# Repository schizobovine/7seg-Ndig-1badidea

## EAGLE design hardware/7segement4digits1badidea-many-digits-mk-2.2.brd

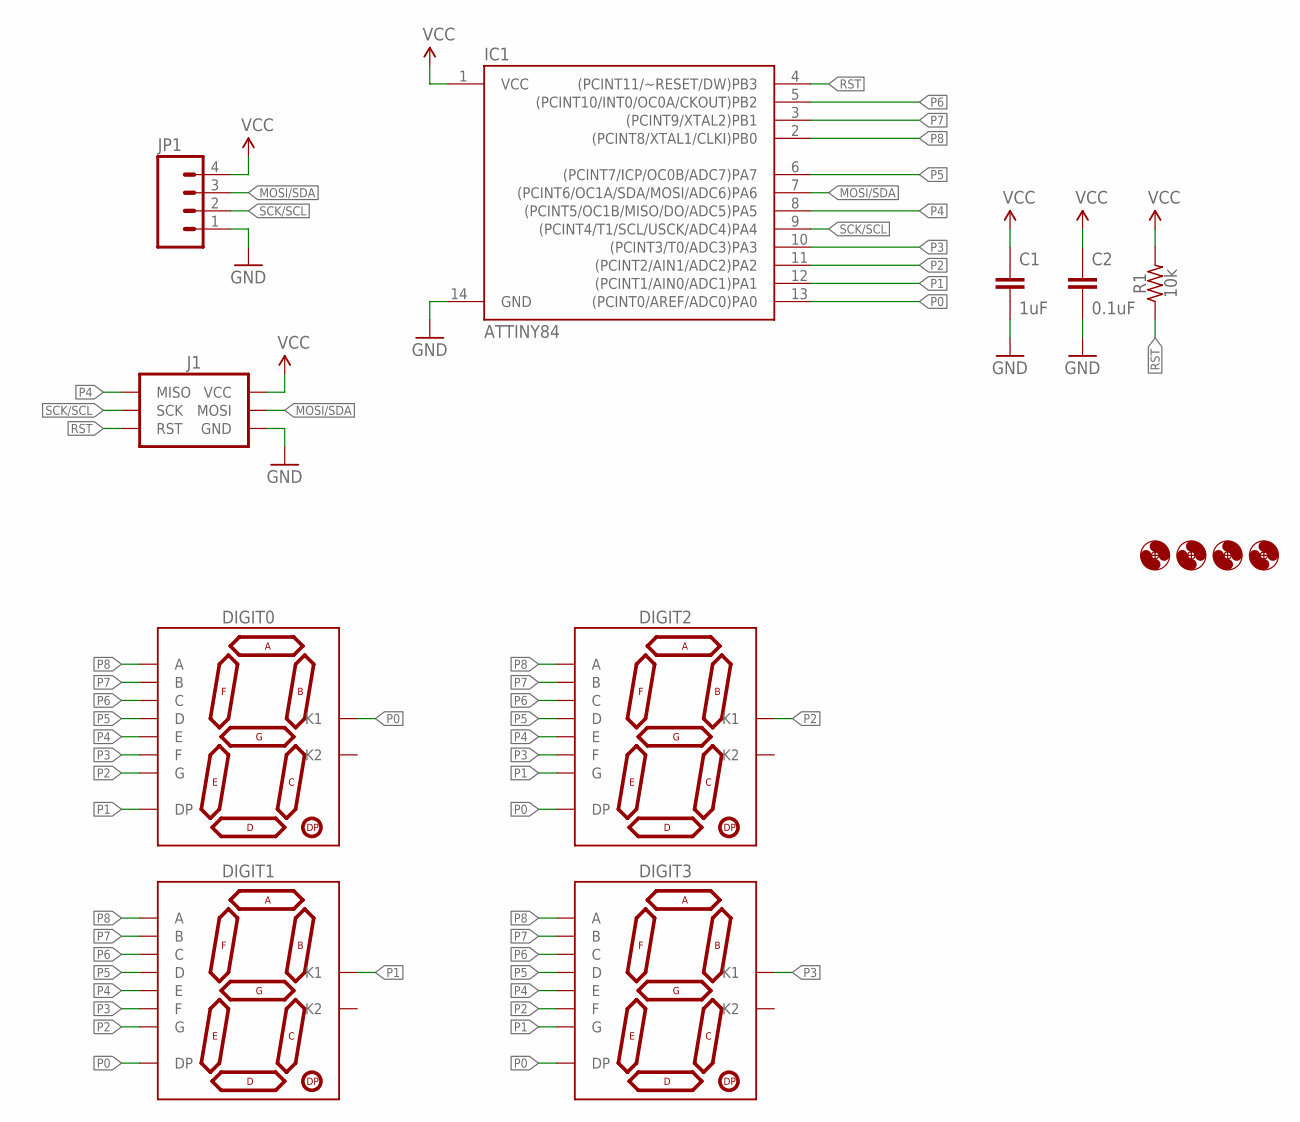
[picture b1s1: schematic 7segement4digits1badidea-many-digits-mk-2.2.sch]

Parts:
C1: 1uF; C0805
C2: 0.1uF; C0603
DIGIT0, DIGIT1, DIGIT2, DIGIT3: 7SEG_1DIGPTH-25.4MM; 7SEG_1DIG_25.4MM
H1, H2, H3, H4: HOLE#2; HOLE-#2
IC1: ATTINY84; SO14
J1: AVR_SPI_PRG_6PTH; 2X3
JP1: M04PTH; 1X04-PTH-VERT
R1: 10k; R0603

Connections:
GND: C1.2, C2.2, IC1.14 (GND), J1.6 (GND), JP1.1
MOSI/SDA: IC1.7 ((PCINT6/OC1A/SDA/MOSI/ADC6)PA6), J1.4 (MOSI), JP1.3
P0: DIGIT0.3 (K1), DIGIT1.5 (DP), DIGIT2.5 (DP), DIGIT3.5 (DP), IC1.13 ((PCINT0/AREF/ADC0)PA0)
P1: DIGIT0.5 (DP), DIGIT1.3 (K1), DIGIT2.10 (G), DIGIT3.10 (G), IC1.12 ((PCINT1/AIN0/ADC1)PA1)
P2: DIGIT0.10 (G), DIGIT1.10 (G), DIGIT2.3 (K1), DIGIT3.9 (F), IC1.11 ((PCINT2/AIN1/ADC2)PA2)
P3: DIGIT0.9 (F), DIGIT1.9 (F), DIGIT2.9 (F), DIGIT3.3 (K1), IC1.10 ((PCINT3/T0/ADC3)PA3)
P4: DIGIT0.1 (E), DIGIT1.1 (E), DIGIT2.1 (E), DIGIT3.1 (E), IC1.8 ((PCINT5/OC1B/MISO/DO/ADC5)PA5), J1.1 (MISO)
P5: DIGIT0.2 (D), DIGIT1.2 (D), DIGIT2.2 (D), DIGIT3.2 (D), IC1.6 ((PCINT7/ICP/OC0B/ADC7)PA7)
P6: DIGIT0.4 (C), DIGIT1.4 (C), DIGIT2.4 (C), DIGIT3.4 (C), IC1.5 ((PCINT10/INT0/OC0A/CKOUT)PB2)
P7: DIGIT0.6 (B), DIGIT1.6 (B), DIGIT2.6 (B), DIGIT3.6 (B), IC1.3 ((PCINT9/XTAL2)PB1)
P8: DIGIT0.7 (A), DIGIT1.7 (A), DIGIT2.7 (A), DIGIT3.7 (A), IC1.2 ((PCINT8/XTAL1/CLKI)PB0)
RST: IC1.4 ((PCINT11/~RESET/DW)PB3), J1.5 (RST), R1.1
SCK/SCL: IC1.9 ((PCINT4/T1/SCL/USCK/ADC4)PA4), J1.3 (SCK), JP1.2
VCC: C1.1, C2.1, IC1.1 (VCC), J1.2 (VCC), JP1.4, R1.2

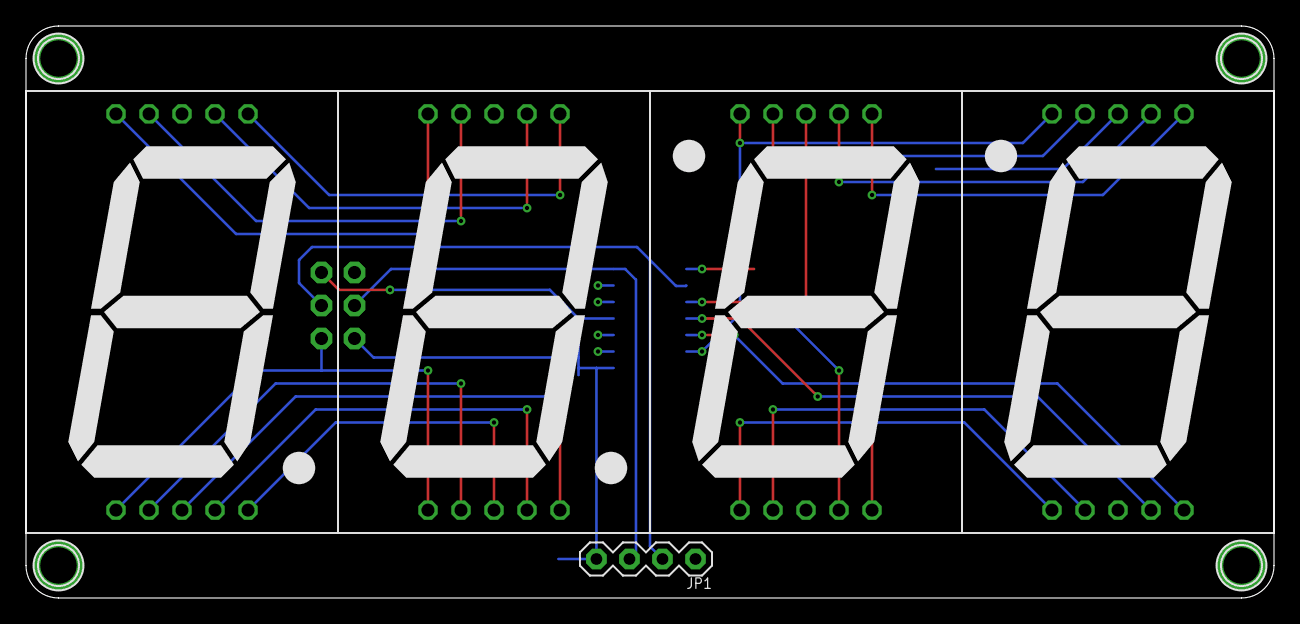
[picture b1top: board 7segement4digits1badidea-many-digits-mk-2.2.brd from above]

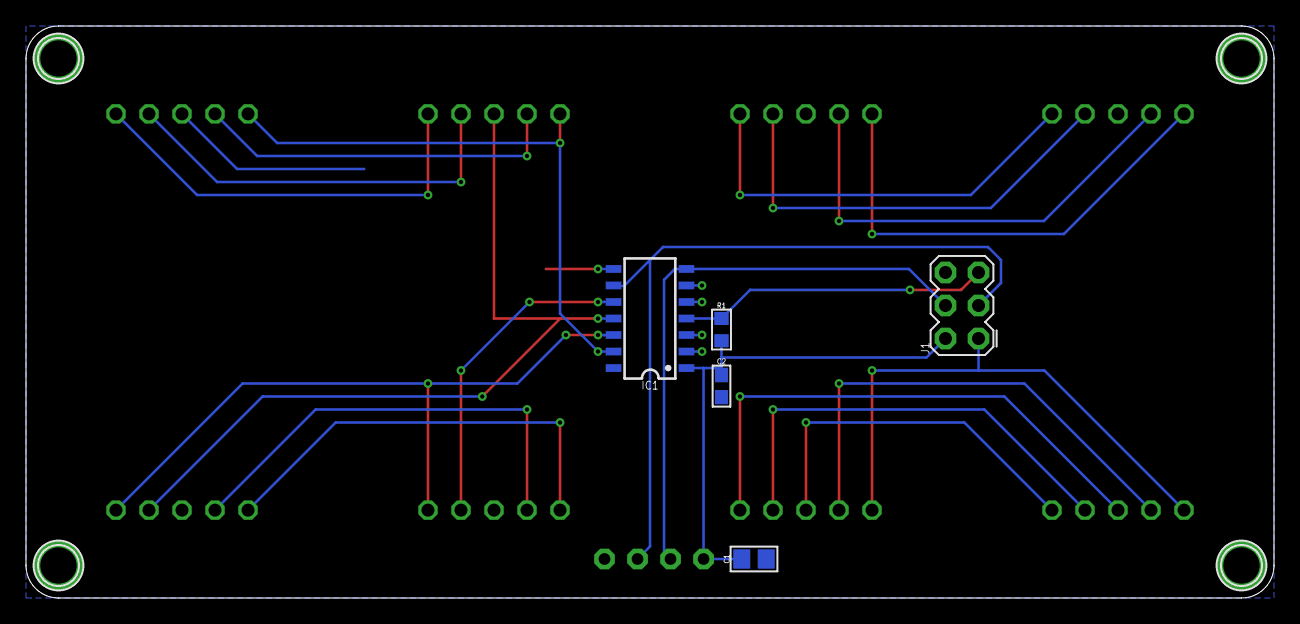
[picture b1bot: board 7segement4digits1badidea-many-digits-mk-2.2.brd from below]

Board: 2 copper layers, 96.0 x 44.0 mm, 14 parts (5 on the bottom side), 14 nets.

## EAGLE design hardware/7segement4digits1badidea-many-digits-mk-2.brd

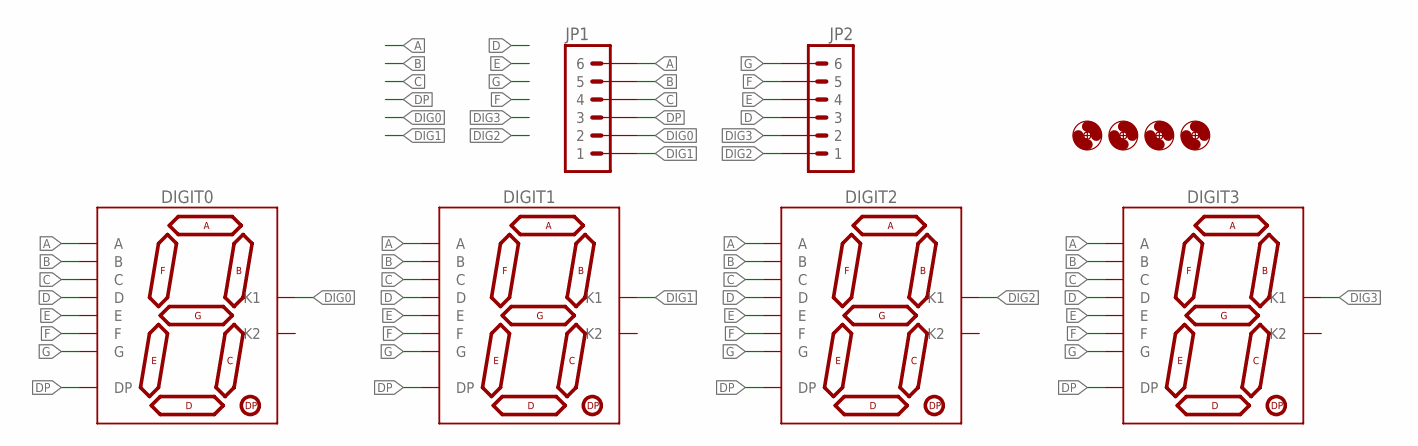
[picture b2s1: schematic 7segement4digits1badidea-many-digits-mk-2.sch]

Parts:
DIGIT0, DIGIT1, DIGIT2, DIGIT3: 7SEG_1DIGPTH-25.4MM; 7SEG_1DIG_25.4MM
H1, H2, H3, H4: HOLE#2; HOLE-#2
JP1, JP2: M06-NOBS-PTH; 1X06_NOLOCK_FUCKITALL

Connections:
A: DIGIT0.7 (A), DIGIT1.7 (A), DIGIT2.7 (A), DIGIT3.7 (A), JP1.6
B: DIGIT0.6 (B), DIGIT1.6 (B), DIGIT2.6 (B), DIGIT3.6 (B), JP1.5
C: DIGIT0.4 (C), DIGIT1.4 (C), DIGIT2.4 (C), DIGIT3.4 (C), JP1.4
D: DIGIT0.2 (D), DIGIT1.2 (D), DIGIT2.2 (D), DIGIT3.2 (D), JP2.3
DIG0: DIGIT0.3 (K1), JP1.2
DIG1: DIGIT1.3 (K1), JP1.1
DIG2: DIGIT2.3 (K1), JP2.1
DIG3: DIGIT3.3 (K1), JP2.2
DP: DIGIT0.5 (DP), DIGIT1.5 (DP), DIGIT2.5 (DP), DIGIT3.5 (DP), JP1.3
E: DIGIT0.1 (E), DIGIT1.1 (E), DIGIT2.1 (E), DIGIT3.1 (E), JP2.4
F: DIGIT0.9 (F), DIGIT1.9 (F), DIGIT2.9 (F), DIGIT3.9 (F), JP2.5
G: DIGIT0.10 (G), DIGIT1.10 (G), DIGIT2.10 (G), DIGIT3.10 (G), JP2.6

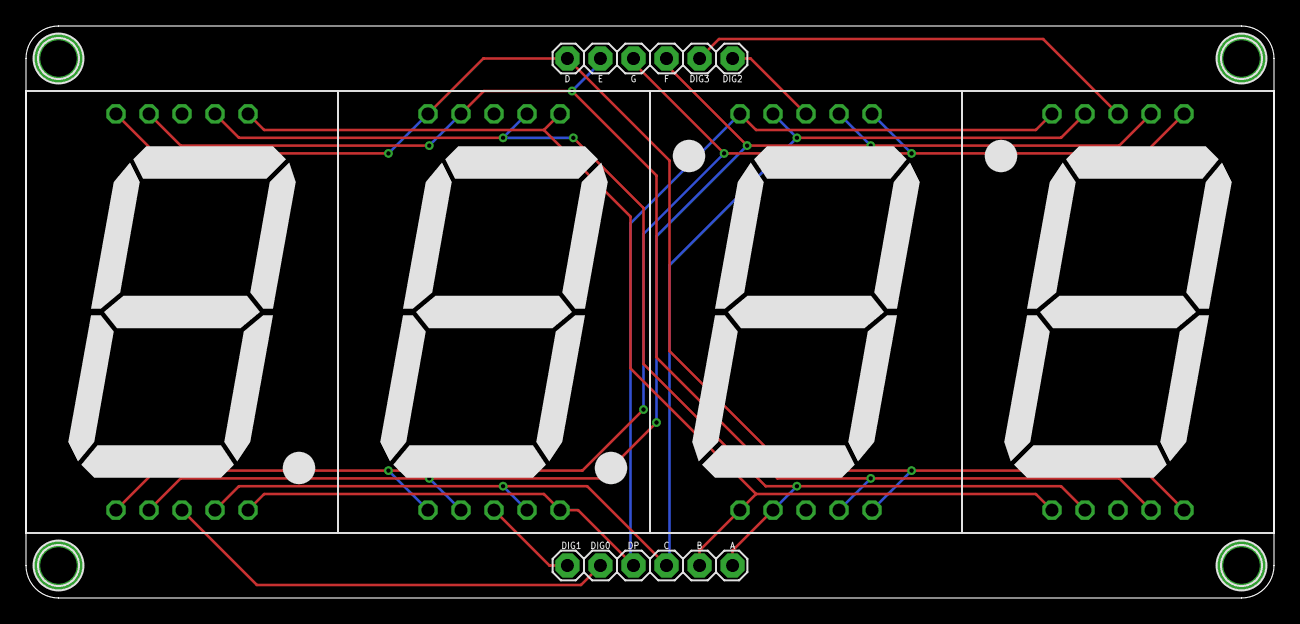
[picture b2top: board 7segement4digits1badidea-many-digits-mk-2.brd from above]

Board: 2 copper layers, 96.0 x 44.0 mm, 10 parts (0 on the bottom side), 12 nets.

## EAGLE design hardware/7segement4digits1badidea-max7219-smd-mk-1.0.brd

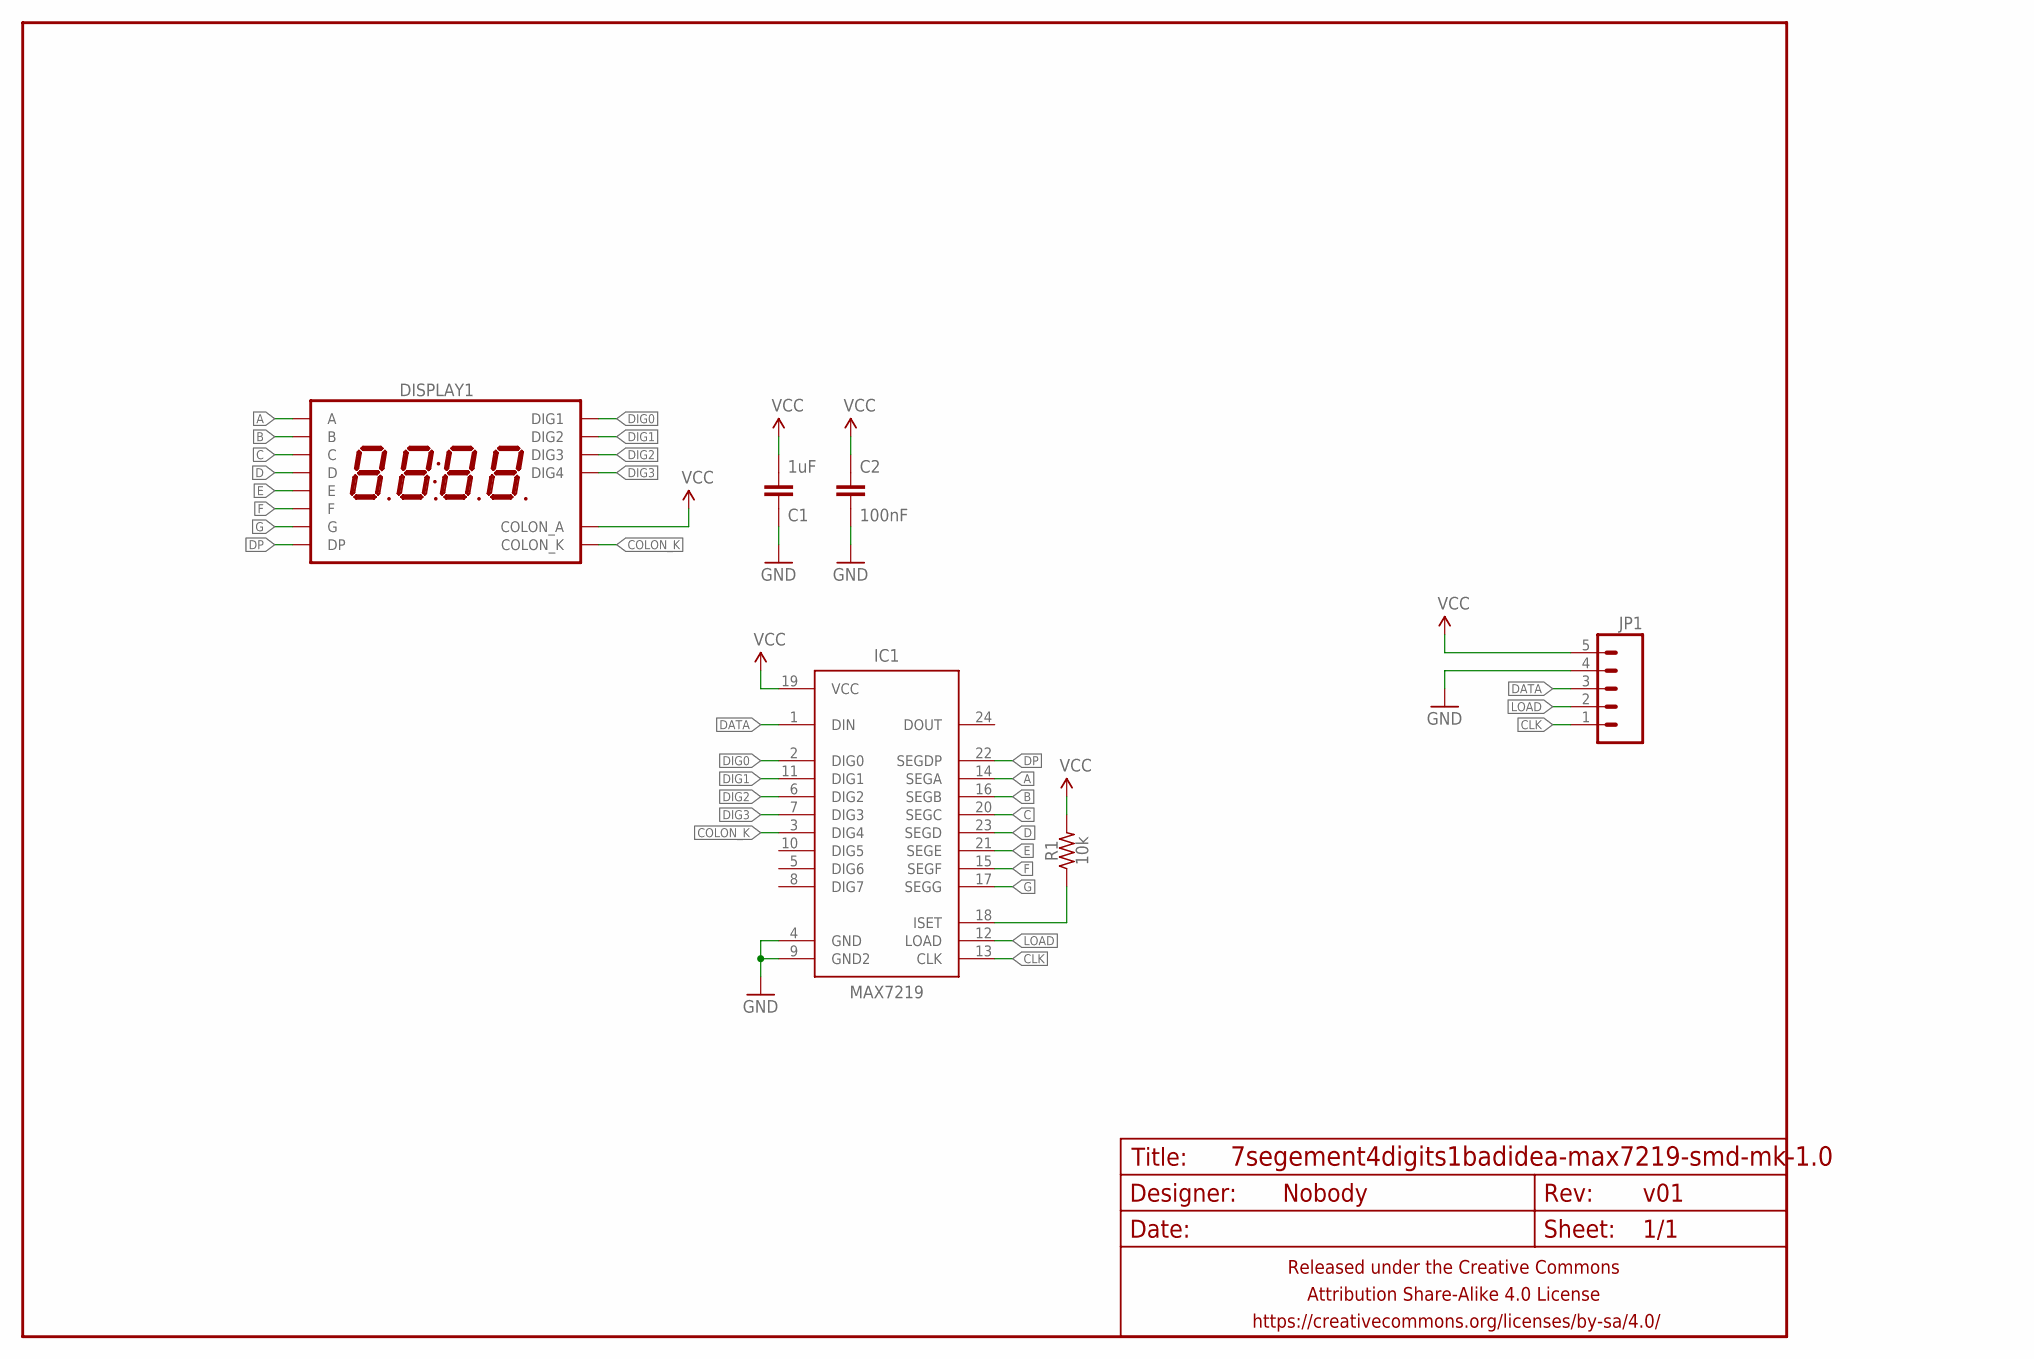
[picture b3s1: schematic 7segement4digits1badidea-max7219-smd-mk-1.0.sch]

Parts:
C1: 1uF; C0805
C2: 100nF; C0805
DISPLAY1: 7SEG_4DIGIT_COLONADAFRUIT_0.56IN; 7SEG_4DIG
FRAME1: FRAME-LETTERNO_PACKAGE; DUMMY
IC1: MAX7219; SO24W
JP1: M05JST-PH-VERT-PTH; JST-5-PH-VERT-PTH
R1: 10k; R0805

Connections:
A: DISPLAY1.P$13 (A), IC1.14 (SEGA)
B: DISPLAY1.P$9 (B), IC1.16 (SEGB)
C: DISPLAY1.P$4 (C), IC1.20 (SEGC)
CLK: IC1.13 (CLK), JP1.1
COLON_K: DISPLAY1.P$7 (COLON_K), IC1.3 (DIG4)
D: DISPLAY1.P$2 (D), IC1.23 (SEGD)
DATA: IC1.1 (DIN), JP1.3
DIG0: DISPLAY1.P$14 (DIG1), IC1.2 (DIG0)
DIG1: DISPLAY1.P$11 (DIG2), IC1.11 (DIG1)
DIG2: DISPLAY1.P$10 (DIG3), IC1.6 (DIG2)
DIG3: DISPLAY1.P$6 (DIG4), IC1.7 (DIG3)
DP: DISPLAY1.P$3 (DP), IC1.22 (SEGDP)
E: DISPLAY1.P$1 (E), IC1.21 (SEGE)
F: DISPLAY1.P$12 (F), IC1.15 (SEGF)
G: DISPLAY1.P$5 (G), IC1.17 (SEGG)
GND: C1.1, C2.2, IC1.4 (GND), IC1.9 (GND2), JP1.4
LOAD: IC1.12 (LOAD), JP1.2
unnamed: IC1.18 (ISET), R1.1
VCC: C1.2, C2.1, DISPLAY1.P$8 (COLON_A), IC1.19 (VCC), JP1.5, R1.2

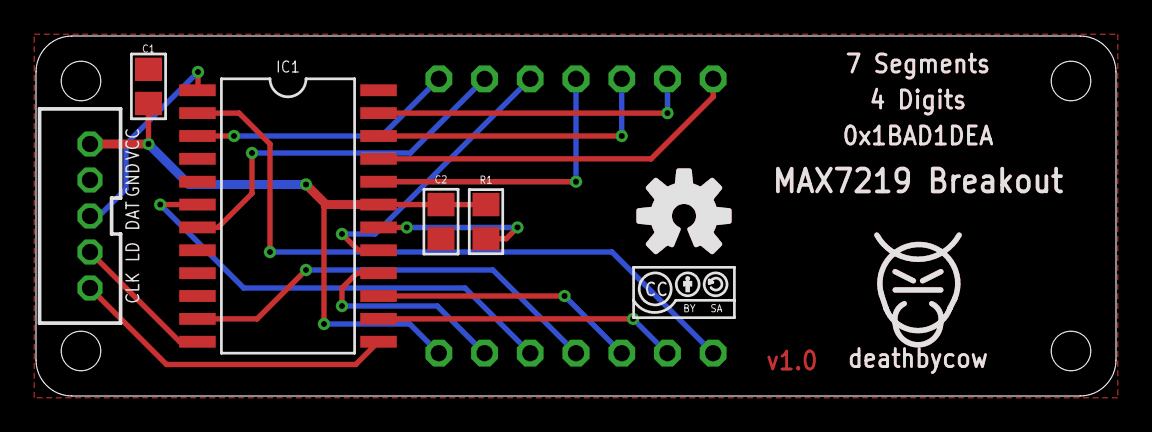
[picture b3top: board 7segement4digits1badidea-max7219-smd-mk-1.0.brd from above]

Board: 2 copper layers, 60.0 x 20.0 mm, 10 parts (1 on the bottom side), 19 nets.

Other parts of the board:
U$1: CC-BY-SA-4.0-NO-URL
U$2: COW_SMALL_METAL
U$3: OSHWLOGO_TOP_0.2_A

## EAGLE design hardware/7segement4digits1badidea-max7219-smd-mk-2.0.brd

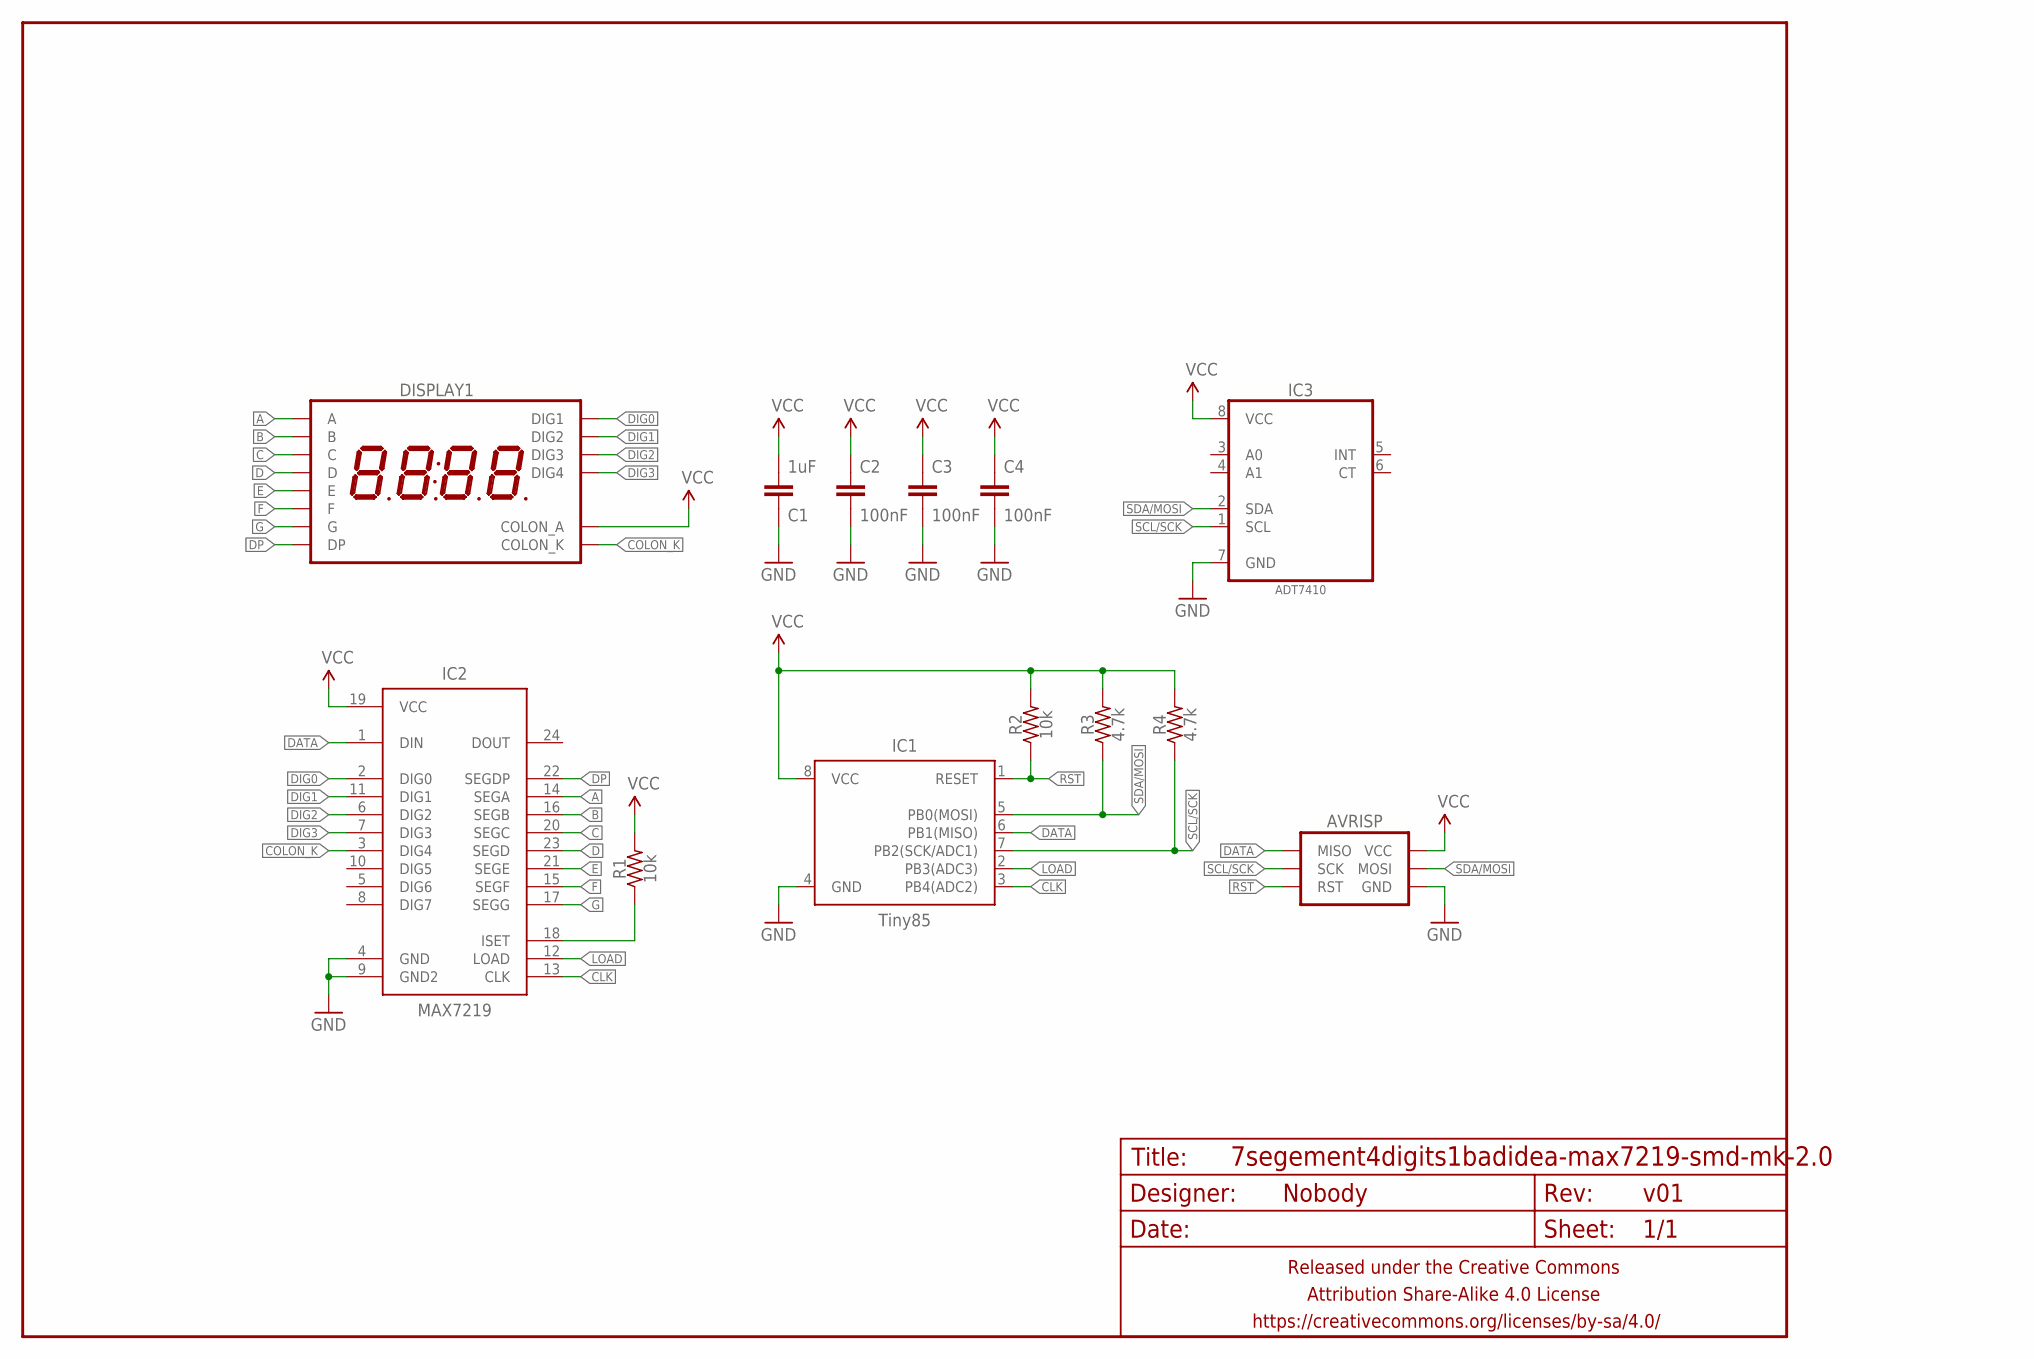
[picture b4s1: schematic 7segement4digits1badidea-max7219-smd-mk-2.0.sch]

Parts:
AVRISP: AVR_SPI_PRG_6PTH; 2X3
C1: 1uF; C0805
C2, C3, C4: 100nF; C0805
DISPLAY1: 7SEG_4DIGIT_COLONADAFRUIT_0.56IN; 7SEG_4DIG
FRAME1: FRAME-LETTERNO_PACKAGE; DUMMY
IC1: Tiny85; SO08-EIAJ
IC2: MAX7219; SO24W
IC3: ADT7410; SOIC127P600X175-8N
R1, R2: 10k; R0805
R3, R4: 4.7k; R0805

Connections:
A: DISPLAY1.P$13 (A), IC2.14 (SEGA)
B: DISPLAY1.P$9 (B), IC2.16 (SEGB)
C: DISPLAY1.P$4 (C), IC2.20 (SEGC)
CLK: IC1.3 (PB4(ADC2)), IC2.13 (CLK)
COLON_K: DISPLAY1.P$7 (COLON_K), IC2.3 (DIG4)
D: DISPLAY1.P$2 (D), IC2.23 (SEGD)
DATA: AVRISP.1 (MISO), IC1.6 (PB1(MISO)), IC2.1 (DIN)
DIG0: DISPLAY1.P$14 (DIG1), IC2.2 (DIG0)
DIG1: DISPLAY1.P$11 (DIG2), IC2.11 (DIG1)
DIG2: DISPLAY1.P$10 (DIG3), IC2.6 (DIG2)
DIG3: DISPLAY1.P$6 (DIG4), IC2.7 (DIG3)
DP: DISPLAY1.P$3 (DP), IC2.22 (SEGDP)
E: DISPLAY1.P$1 (E), IC2.21 (SEGE)
F: DISPLAY1.P$12 (F), IC2.15 (SEGF)
G: DISPLAY1.P$5 (G), IC2.17 (SEGG)
GND: AVRISP.6 (GND), C1.1, C2.2, C3.2, C4.2, IC1.4 (GND), IC2.4 (GND), IC2.9 (GND2), IC3.7 (GND)
LOAD: IC1.2 (PB3(ADC3)), IC2.12 (LOAD)
unnamed: IC2.18 (ISET), R1.1
RST: AVRISP.5 (RST), IC1.1 (RESET), R2.1
SCL/SCK: AVRISP.3 (SCK), IC1.7 (PB2(SCK/ADC1)), IC3.1 (SCL), R4.1
SDA/MOSI: AVRISP.4 (MOSI), IC1.5 (PB0(MOSI)), IC3.2 (SDA), R3.1
VCC: AVRISP.2 (VCC), C1.2, C2.1, C3.1, C4.1, DISPLAY1.P$8 (COLON_A), IC1.8 (VCC), IC2.19 (VCC), IC3.8 (VCC), R1.2, R2.2, R3.2, R4.2

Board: 2 copper layers, 14 parts (1 on the bottom side), 22 nets, no tracks yet.

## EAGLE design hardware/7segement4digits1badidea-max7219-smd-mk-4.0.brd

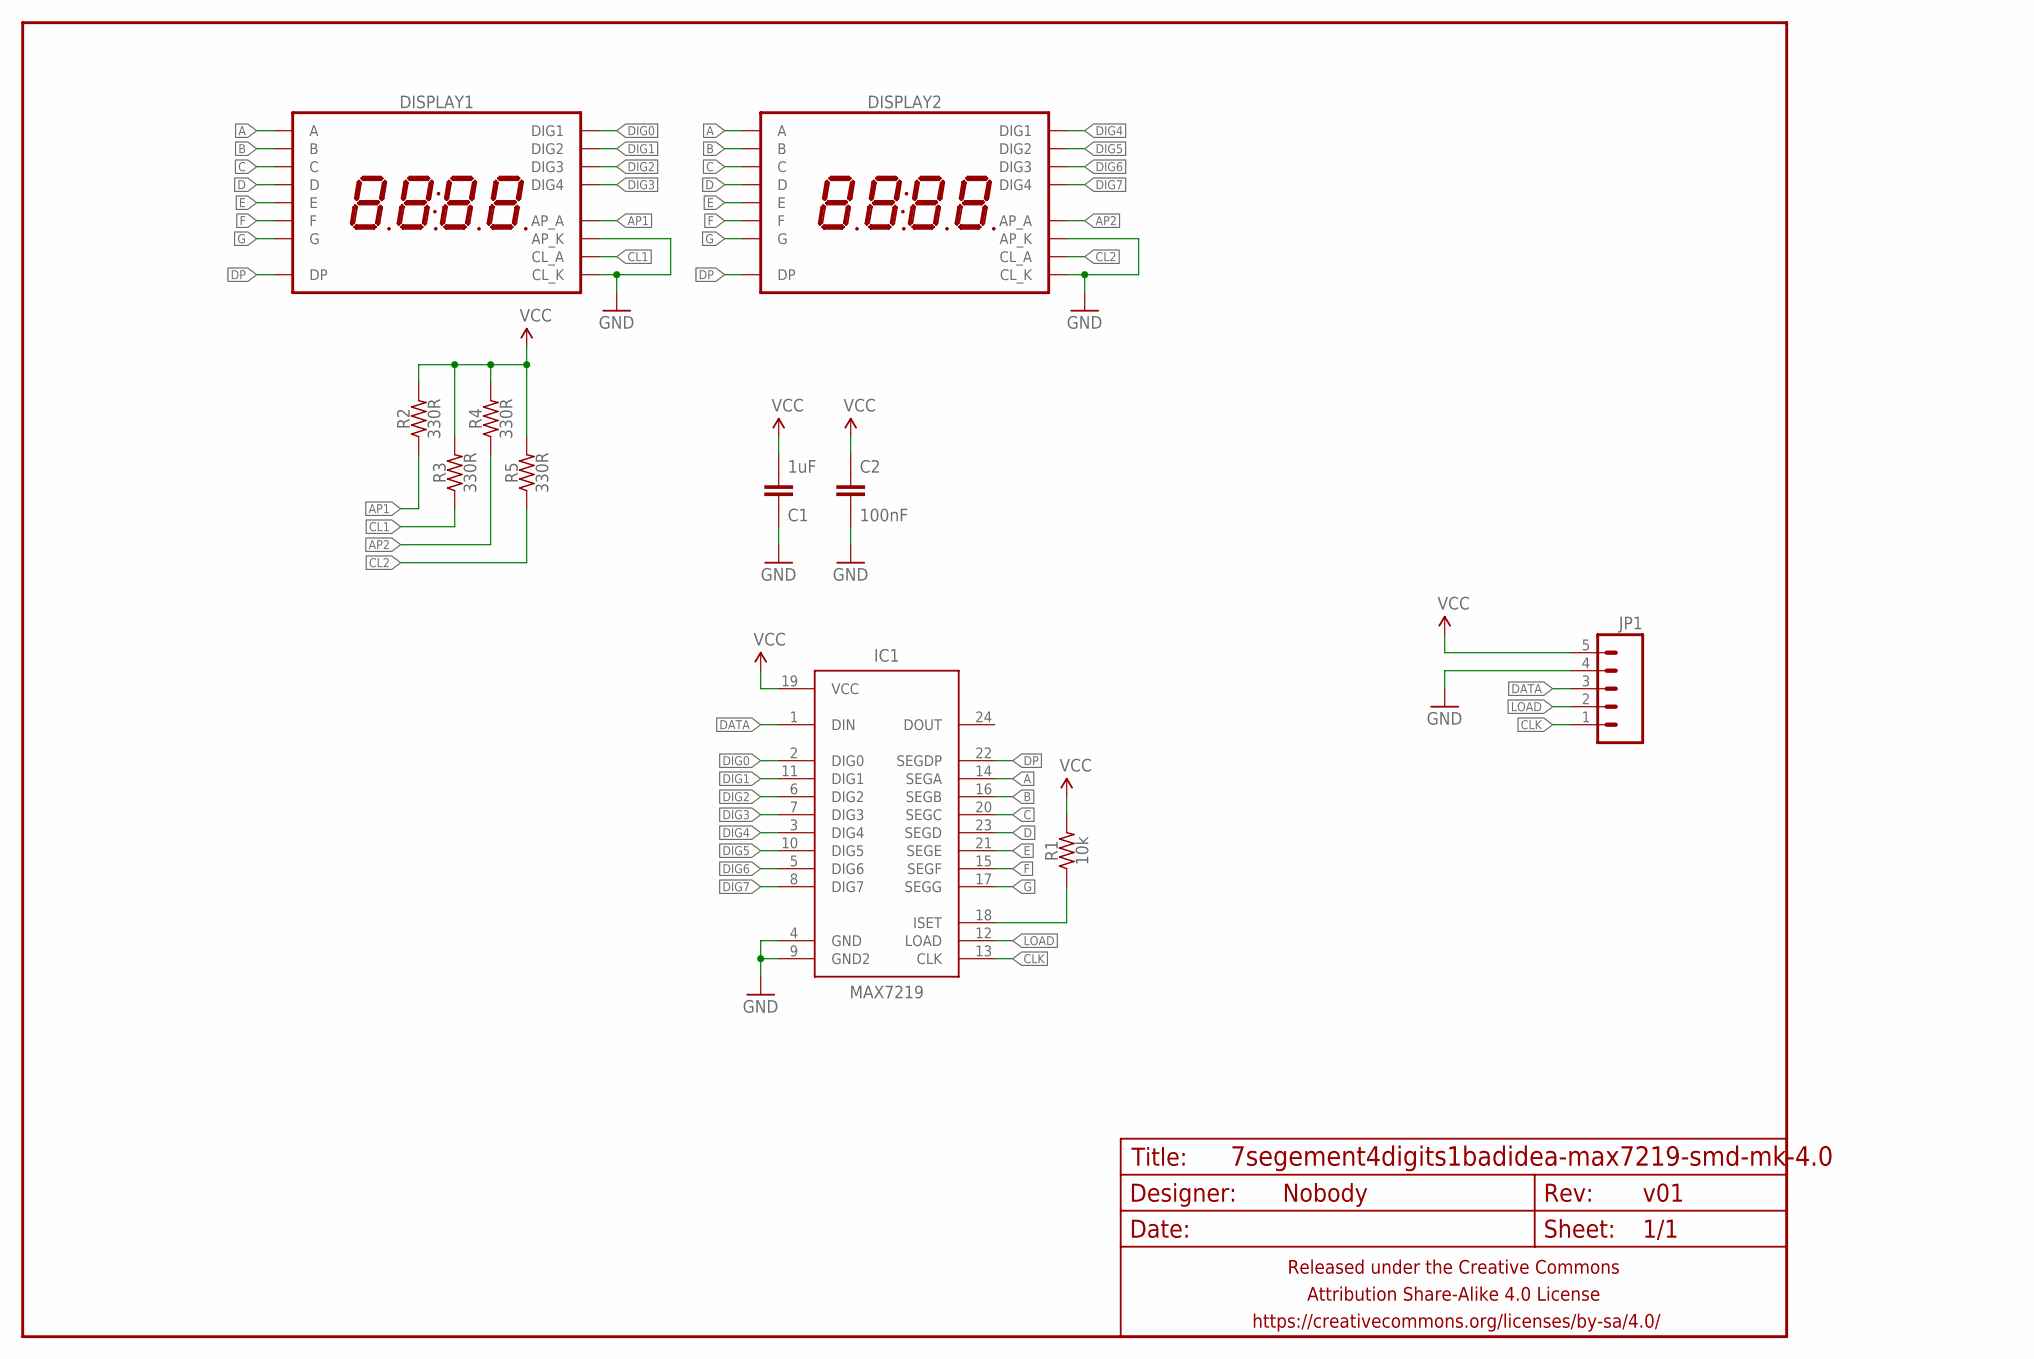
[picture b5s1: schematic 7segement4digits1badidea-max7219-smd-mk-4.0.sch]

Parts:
C1: 1uF; C0805
C2: 100nF; C0805
DISPLAY1, DISPLAY2: 7SEG_4DIGIT_COLON_APOS; 7SEG_4DIG_10MM
FRAME1: FRAME-LETTERNO_PACKAGE; DUMMY
IC1: MAX7219; SO24W
JP1: M05PTH; 1X05
R1: 10k; R0805
R2, R3, R4, R5: 330R; R0805

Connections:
A: DISPLAY1.14 (A), DISPLAY2.14 (A), IC1.14 (SEGA)
AP1: DISPLAY1.10 (AP_A), R2.1
AP2: DISPLAY2.10 (AP_A), R4.1
B: DISPLAY1.16 (B), DISPLAY2.16 (B), IC1.16 (SEGB)
C: DISPLAY1.13 (C), DISPLAY2.13 (C), IC1.20 (SEGC)
CL1: DISPLAY1.4 (CL_A), R3.1
CL2: DISPLAY2.4 (CL_A), R5.1
CLK: IC1.13 (CLK), JP1.1
D: DISPLAY1.3 (D), DISPLAY2.3 (D), IC1.23 (SEGD)
DATA: IC1.1 (DIN), JP1.3
DIG0: DISPLAY1.1 (DIG1), IC1.2 (DIG0)
DIG1: DISPLAY1.2 (DIG2), IC1.11 (DIG1)
DIG2: DISPLAY1.6 (DIG3), IC1.6 (DIG2)
DIG3: DISPLAY1.8 (DIG4), IC1.7 (DIG3)
DIG4: DISPLAY2.1 (DIG1), IC1.3 (DIG4)
DIG5: DISPLAY2.2 (DIG2), IC1.10 (DIG5)
DIG6: DISPLAY2.6 (DIG3), IC1.5 (DIG6)
DIG7: DISPLAY2.8 (DIG4), IC1.8 (DIG7)
DP: DISPLAY1.7 (DP), DISPLAY2.7 (DP), IC1.22 (SEGDP)
E: DISPLAY1.5 (E), DISPLAY2.5 (E), IC1.21 (SEGE)
F: DISPLAY1.11 (F), DISPLAY2.11 (F), IC1.15 (SEGF)
G: DISPLAY1.15 (G), DISPLAY2.15 (G), IC1.17 (SEGG)
GND: C1.1, C2.2, DISPLAY1.9 (AP_K), DISPLAY1.12 (CL_K), DISPLAY2.9 (AP_K), DISPLAY2.12 (CL_K), IC1.4 (GND), IC1.9 (GND2), JP1.4
LOAD: IC1.12 (LOAD), JP1.2
unnamed: IC1.18 (ISET), R1.1
VCC: C1.2, C2.1, IC1.19 (VCC), JP1.5, R1.2, R2.2, R3.2, R4.2, R5.2

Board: 2 copper layers, 15 parts (2 on the bottom side), 26 nets, no tracks yet.

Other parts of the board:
U$1: CC-BY-SA-4.0-NO-URL
U$2: COW_SMALL_METAL
U$3: OSHWLOGO_TOP_0.2_A

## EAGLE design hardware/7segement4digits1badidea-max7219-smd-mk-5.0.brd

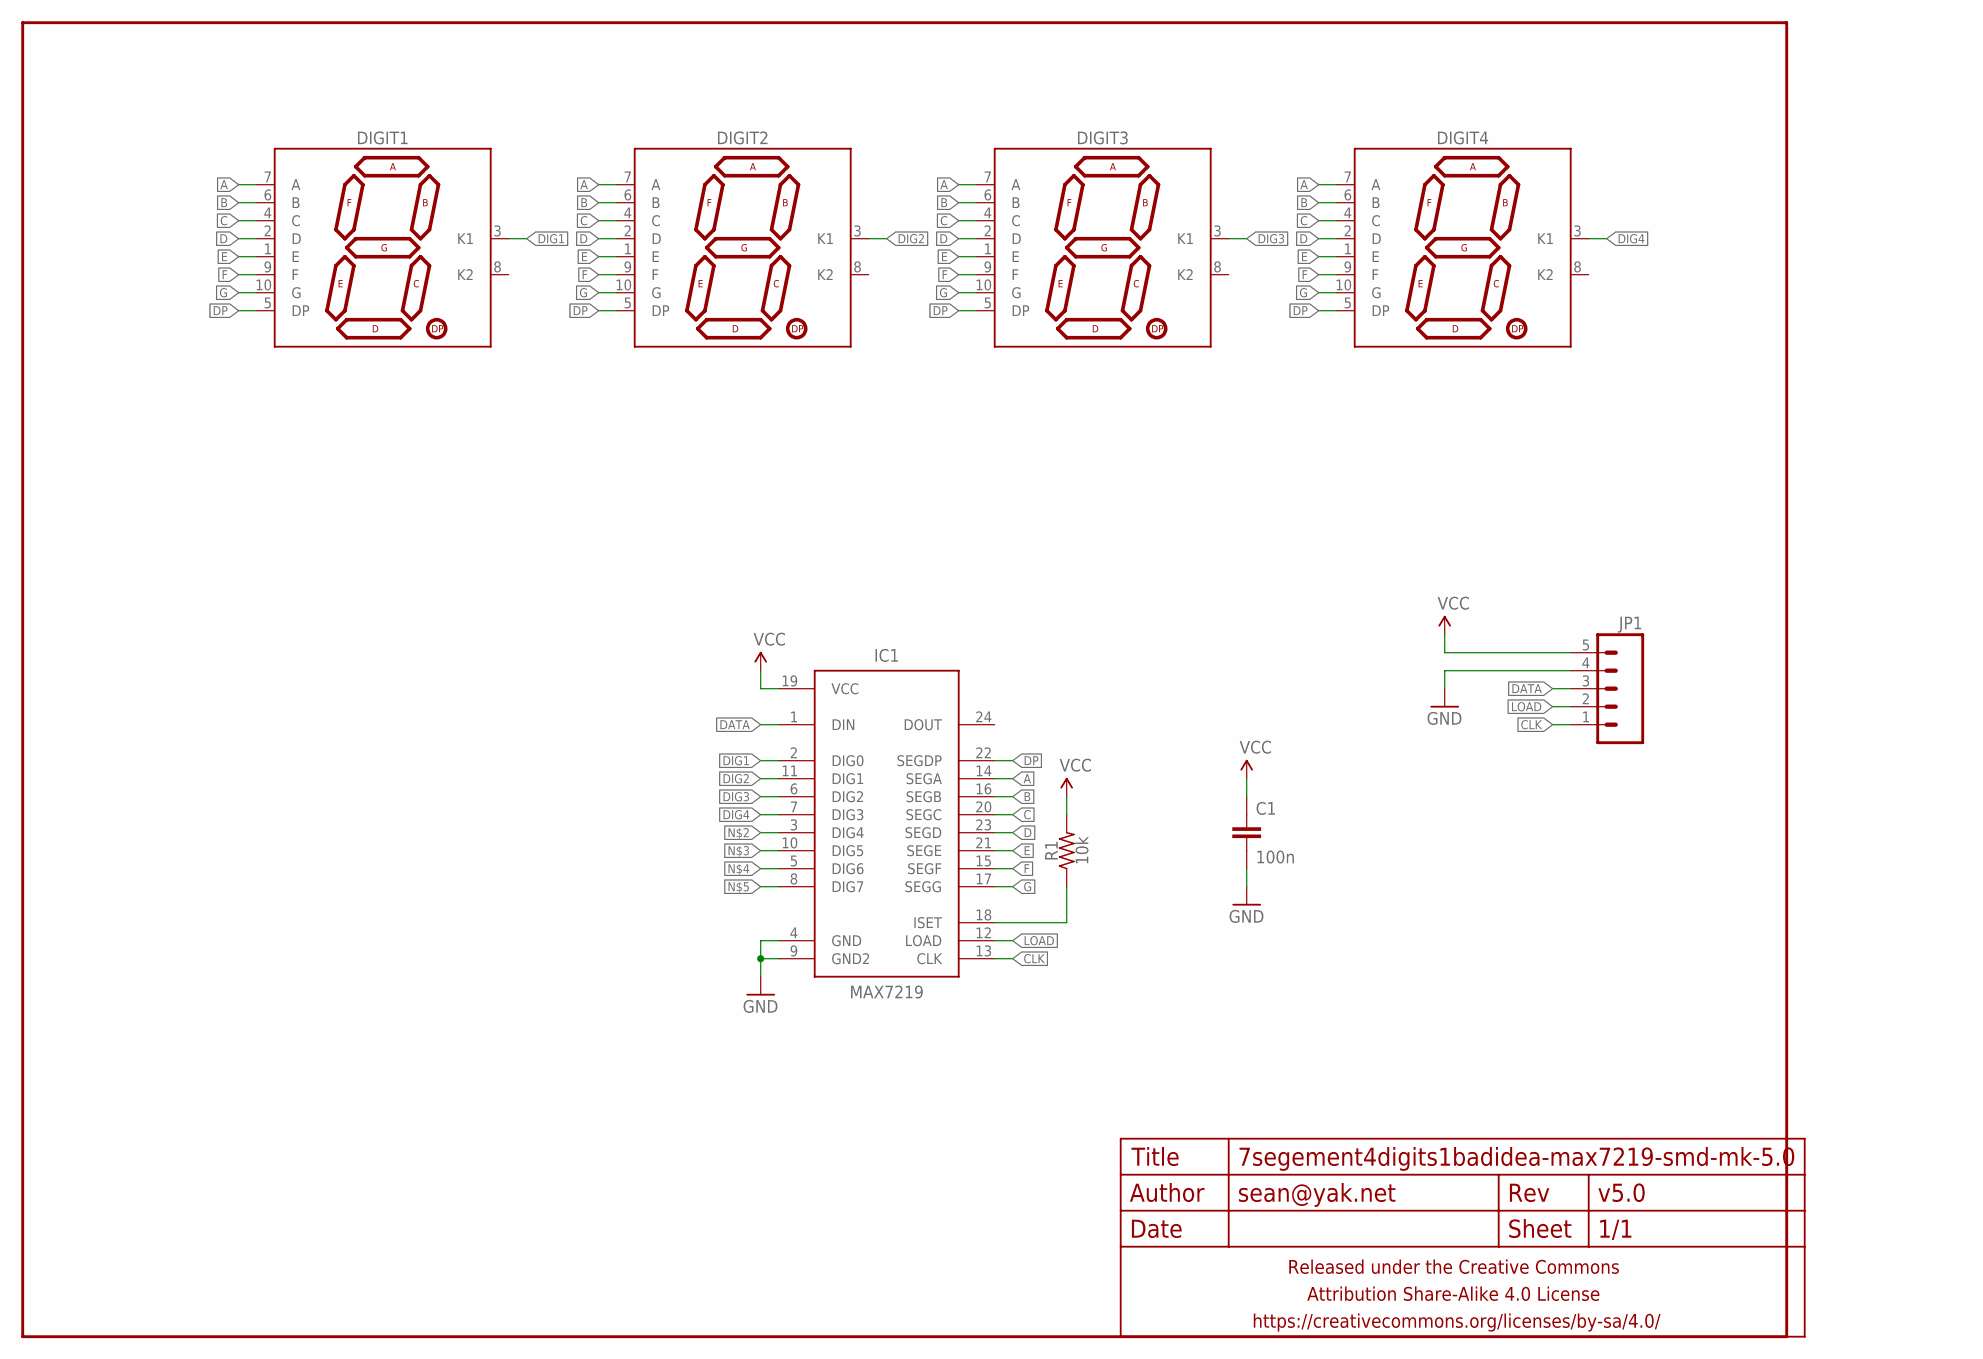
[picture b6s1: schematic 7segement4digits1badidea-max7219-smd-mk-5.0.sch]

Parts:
C1: 100n; C0805
DIGIT1, DIGIT2, DIGIT3, DIGIT4: 7SEG_1DIGPTH-25.4MM; 7SEG_1DIG_25.4MM
FRAME1: FRAME-LETTERNO_PACKAGE; DUMMY
IC1: MAX7219; SO24W
JP1: M05PTH-CENTERED; 1X05_PTH_CENTERED
R1: 10k; R0805

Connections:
A: DIGIT1.7 (A), DIGIT2.7 (A), DIGIT3.7 (A), DIGIT4.7 (A), IC1.14 (SEGA)
B: DIGIT1.6 (B), DIGIT2.6 (B), DIGIT3.6 (B), DIGIT4.6 (B), IC1.16 (SEGB)
C: DIGIT1.4 (C), DIGIT2.4 (C), DIGIT3.4 (C), DIGIT4.4 (C), IC1.20 (SEGC)
CLK: IC1.13 (CLK), JP1.1
D: DIGIT1.2 (D), DIGIT2.2 (D), DIGIT3.2 (D), DIGIT4.2 (D), IC1.23 (SEGD)
DATA: IC1.1 (DIN), JP1.3
DIG1: DIGIT1.3 (K1), IC1.2 (DIG0)
DIG2: DIGIT2.3 (K1), IC1.11 (DIG1)
DIG3: DIGIT3.3 (K1), IC1.6 (DIG2)
DIG4: DIGIT4.3 (K1), IC1.7 (DIG3)
DP: DIGIT1.5 (DP), DIGIT2.5 (DP), DIGIT3.5 (DP), DIGIT4.5 (DP), IC1.22 (SEGDP)
E: DIGIT1.1 (E), DIGIT2.1 (E), DIGIT3.1 (E), DIGIT4.1 (E), IC1.21 (SEGE)
F: DIGIT1.9 (F), DIGIT2.9 (F), DIGIT3.9 (F), DIGIT4.9 (F), IC1.15 (SEGF)
G: DIGIT1.10 (G), DIGIT2.10 (G), DIGIT3.10 (G), DIGIT4.10 (G), IC1.17 (SEGG)
GND: C1.2, IC1.4 (GND), IC1.9 (GND2), JP1.4
LOAD: IC1.12 (LOAD), JP1.2
unnamed: IC1.18 (ISET), R1.1
VCC: C1.1, IC1.19 (VCC), JP1.5, R1.2

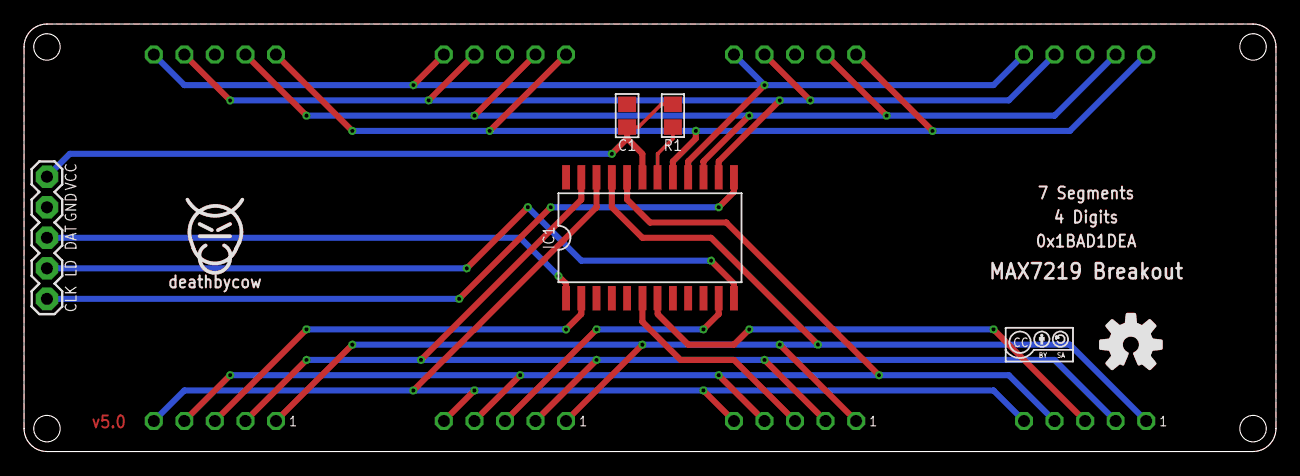
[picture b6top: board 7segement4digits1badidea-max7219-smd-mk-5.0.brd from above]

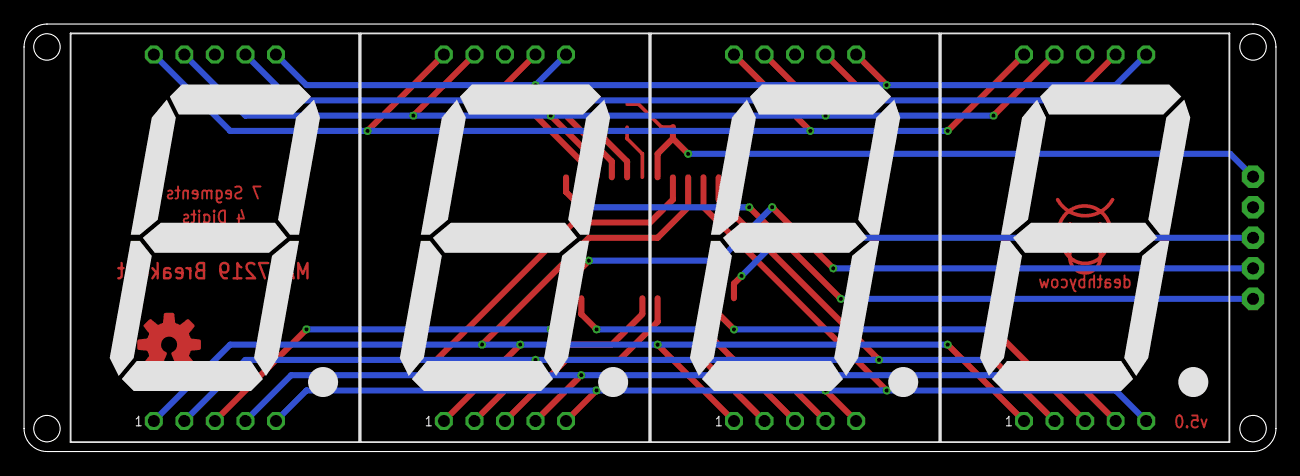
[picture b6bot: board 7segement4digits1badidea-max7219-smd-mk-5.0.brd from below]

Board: 2 copper layers, 104.1 x 35.6 mm, 12 parts (4 on the bottom side), 18 nets.

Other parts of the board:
U$1: CC-BY-SA-4.0-NO-URL
U$2: COW_SMALL_METAL
U$3: OSHWLOGO_TOP_0.2_A

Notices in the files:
parts and their libraries:
A_butts: Released under the Creative Commons Attribution Share-Alike 4.0 License
A_butts: https://creativecommons.org/licenses/by-sa/4.0
A_butts: Released under the Creative Commons
